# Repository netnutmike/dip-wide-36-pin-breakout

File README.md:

# dip-wide-36-pin-breakout
A wide 36 pin DIP breakout board designed specifically for Heltec Lora dev board but will work with anything.

It is a small board with DIP in the middle and pins on the outside for either pheonix connectors or any other tpye of connection that fits the 2.5mm design specification.

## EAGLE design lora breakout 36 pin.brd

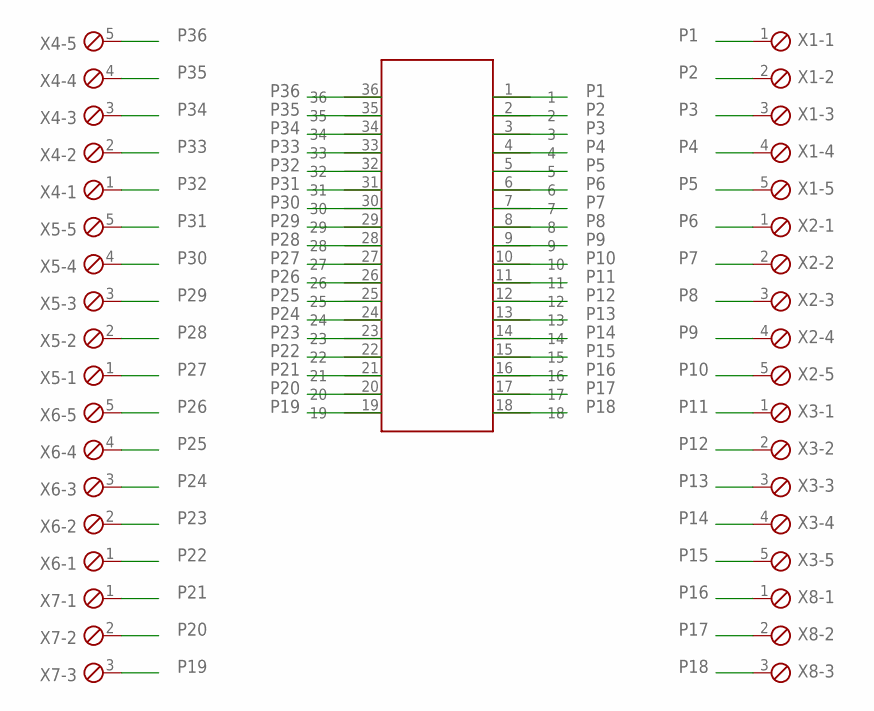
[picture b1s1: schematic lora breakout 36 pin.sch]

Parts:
U$1: HELTECLORA
X1, X2, X3, X4, X5, X6: MPT5; 5POL254
X7, X8: MPT3; 3POL254

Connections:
P1: U$1.1, X1.1
P2: U$1.2, X1.2
P3: U$1.3, X1.3
P4: U$1.4, X1.4
P5: U$1.5, X1.5
P6: U$1.6, X2.1
P7: U$1.7, X2.2
P8: U$1.8, X2.3
P9: U$1.9, X2.4
P10: U$1.10, X2.5
P11: U$1.11, X3.1
P12: U$1.12, X3.2
P13: U$1.13, X3.3
P14: U$1.14, X3.4
P15: U$1.15, X3.5
P16: U$1.16, X8.1
P17: U$1.17, X8.2
P18: U$1.18, X8.3
P19: U$1.19, X7.3
P20: U$1.20, X7.2
P21: U$1.21, X7.1
P22: U$1.22, X6.1
P23: U$1.23, X6.2
P24: U$1.24, X6.3
P25: U$1.25, X6.4
P26: U$1.26, X6.5
P27: U$1.27, X5.1
P28: U$1.28, X5.2
P29: U$1.29, X5.3
P30: U$1.30, X5.4
P31: U$1.31, X5.5
P32: U$1.32, X4.1
P33: U$1.33, X4.2
P34: U$1.34, X4.3
P35: U$1.35, X4.4
P36: U$1.36, X4.5

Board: 2 copper layers, 9 parts (0 on the bottom side), 36 nets, no tracks yet.

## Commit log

2020-12-29 Initial Load
2021-01-22 new design from fusion360
